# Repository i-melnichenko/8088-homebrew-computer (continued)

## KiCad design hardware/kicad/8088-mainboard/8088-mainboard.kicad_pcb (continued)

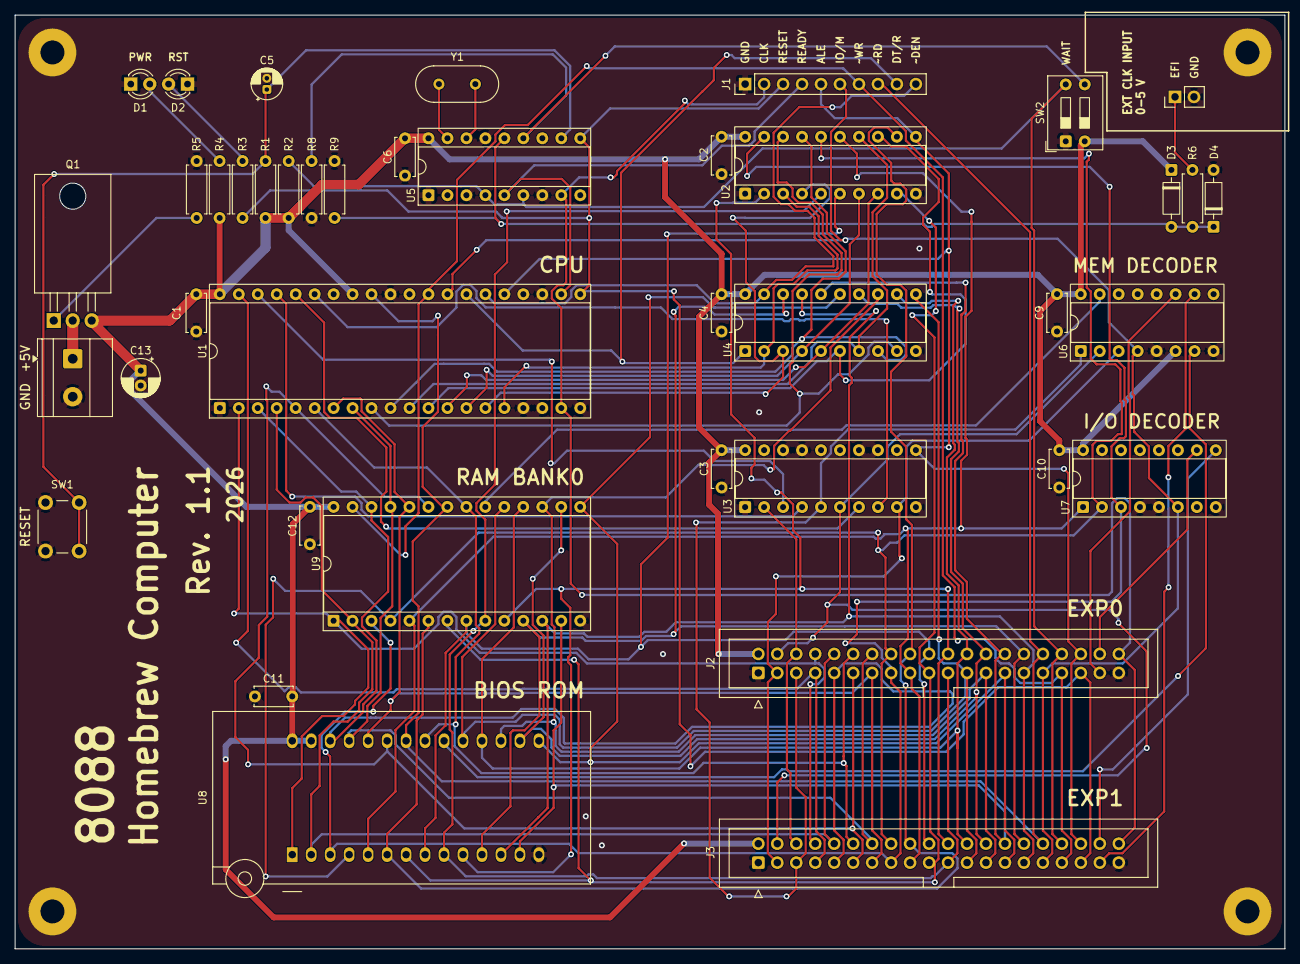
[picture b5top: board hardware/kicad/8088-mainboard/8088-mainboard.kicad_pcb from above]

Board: 2 copper layers, 170.0 x 125.0 mm, 45 parts (0 on the bottom side), 68 nets.
